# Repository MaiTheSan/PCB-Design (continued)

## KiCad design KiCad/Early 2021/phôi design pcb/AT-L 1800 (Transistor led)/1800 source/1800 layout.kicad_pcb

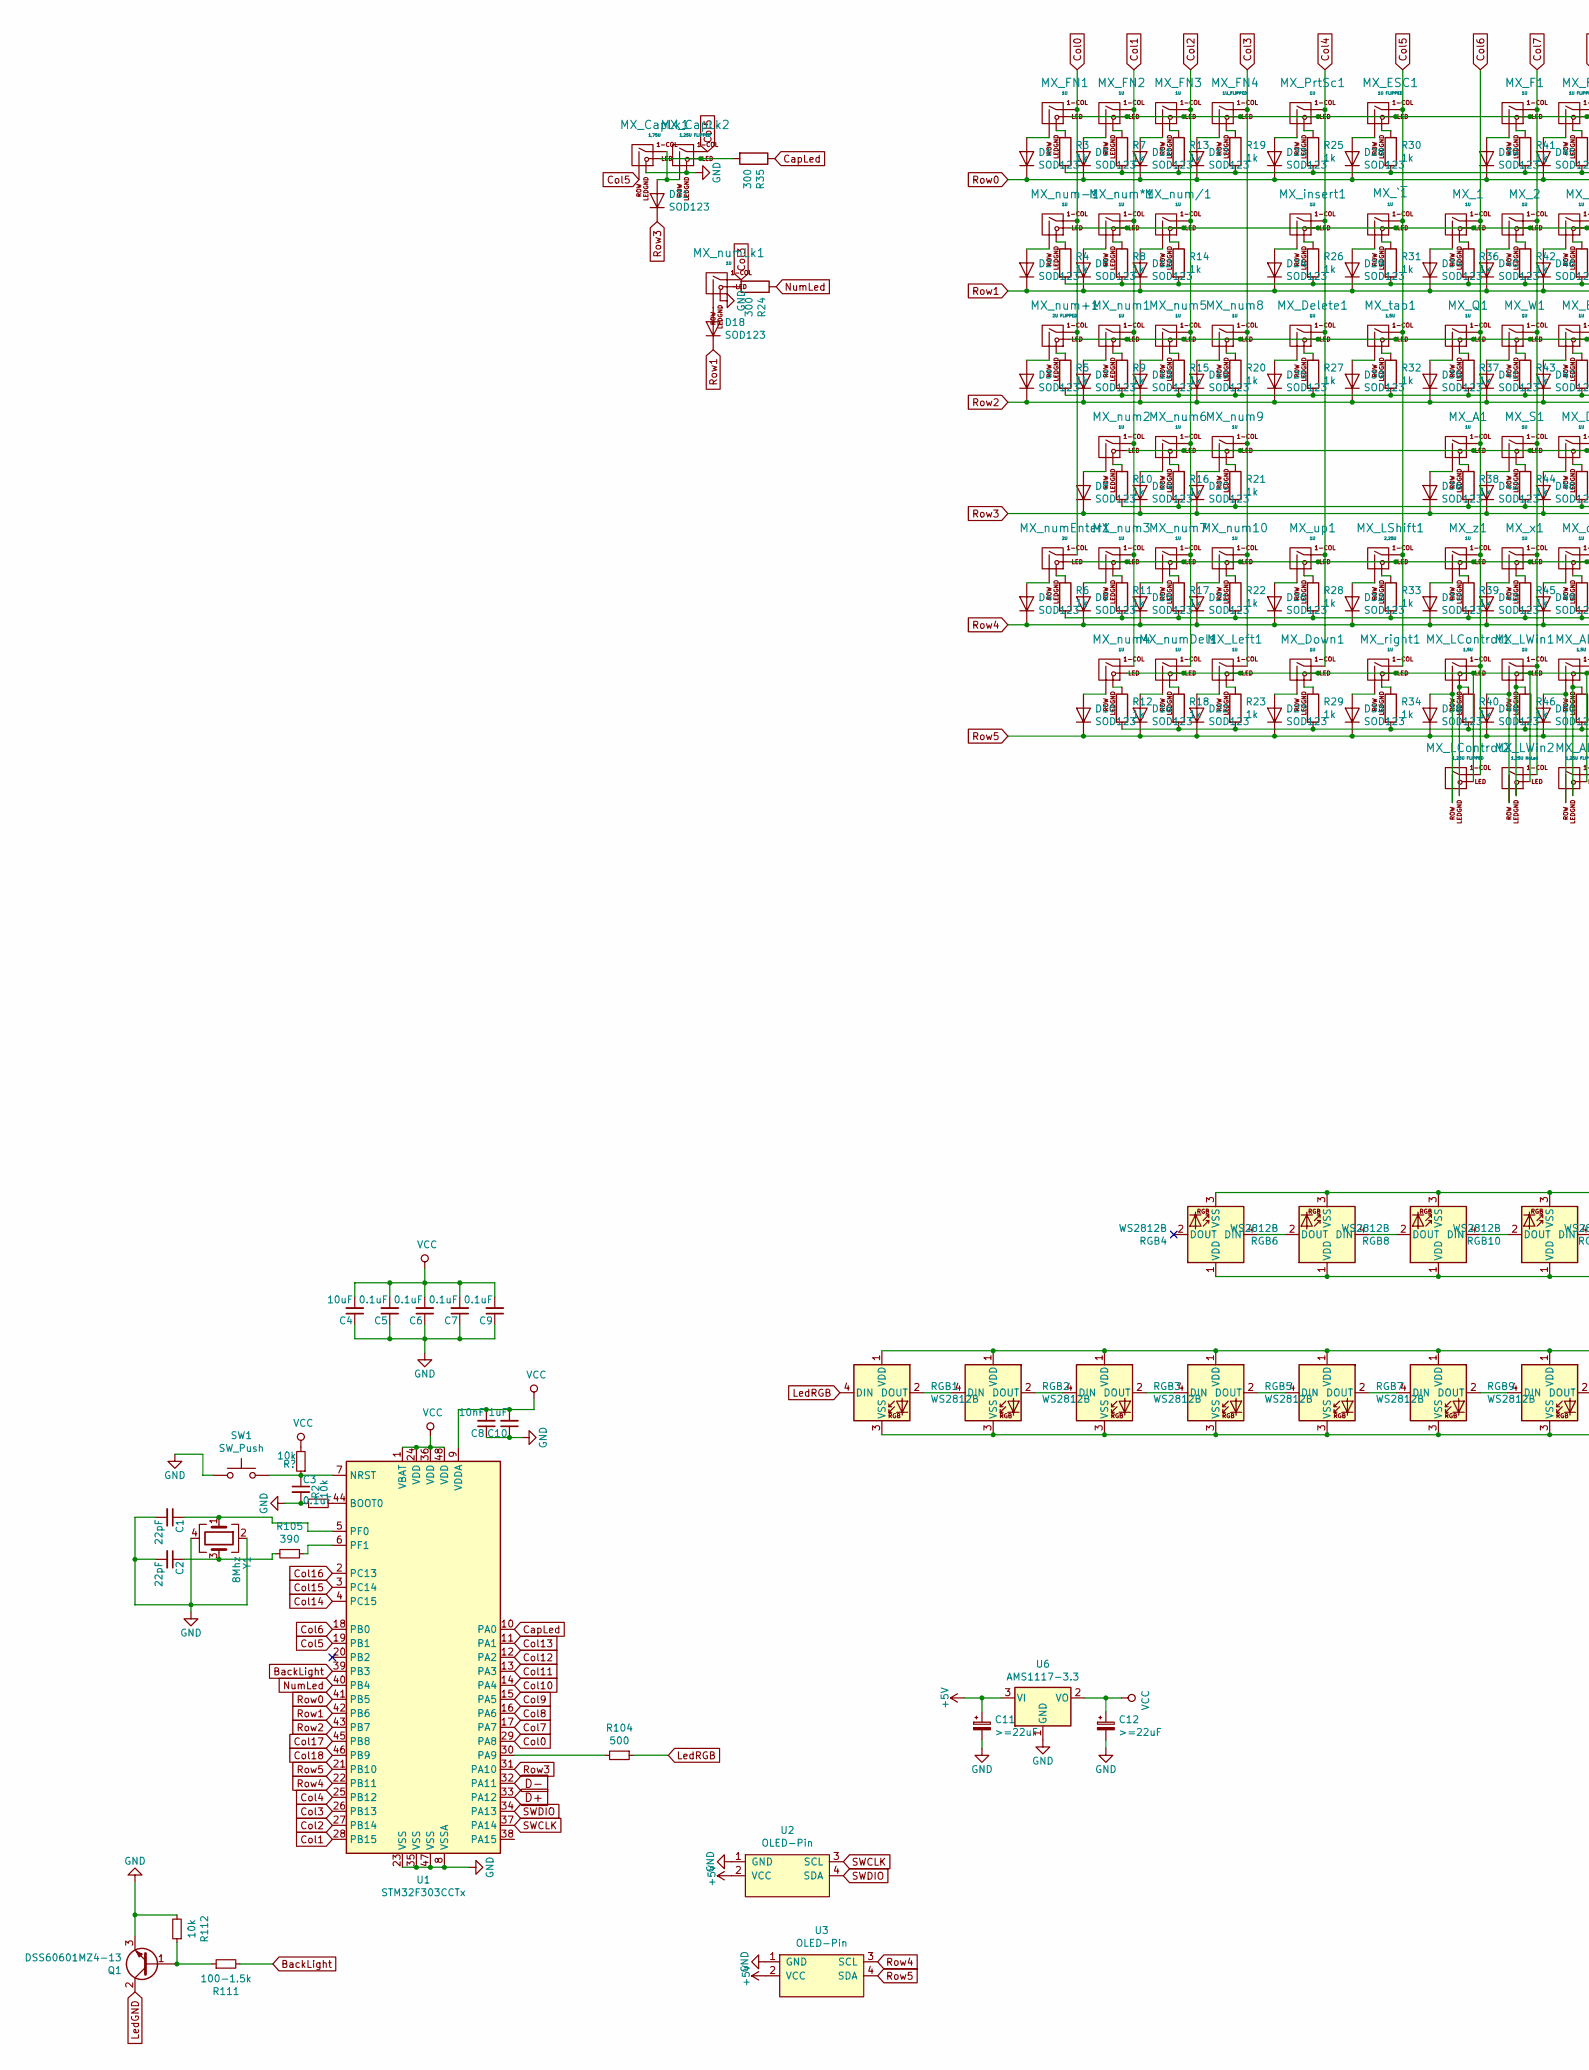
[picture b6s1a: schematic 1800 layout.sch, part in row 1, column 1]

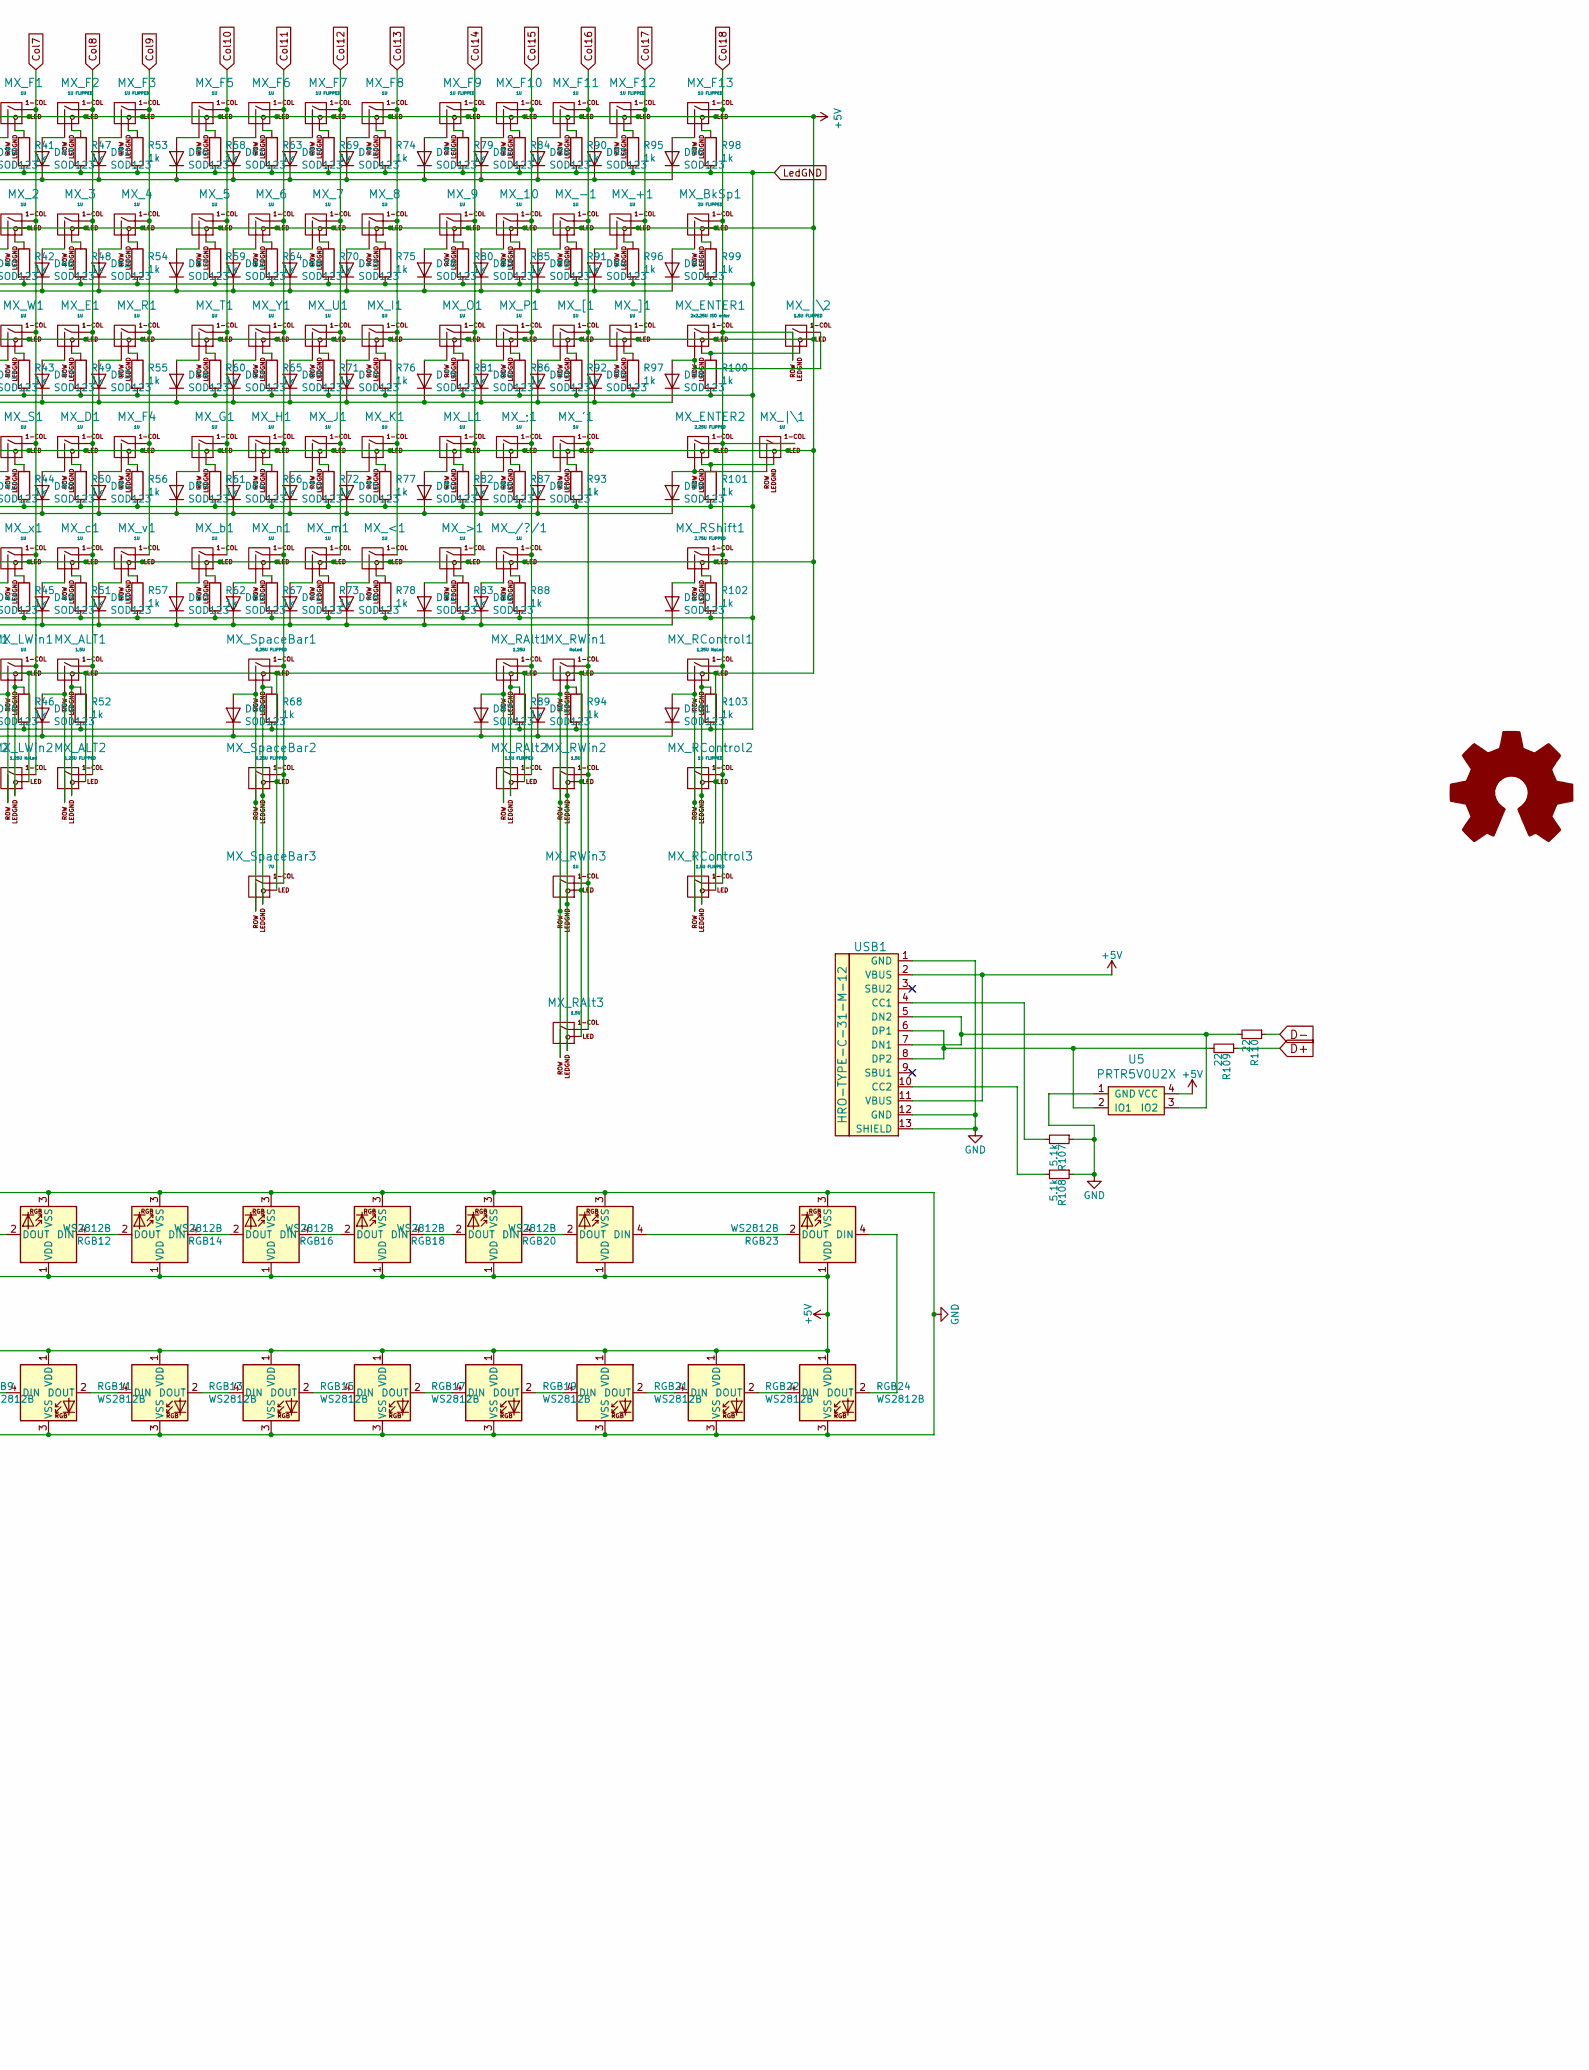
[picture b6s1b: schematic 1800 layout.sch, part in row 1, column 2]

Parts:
C1, C2: 22pF; C_0603
C3, C5, C6, C7, C9: 0.1uF; C_0402_1005Metric
C4: 10uF; C_0603
C8: 10nF; C_0402_1005Metric
C10: 1uF; C_0603
C11, C12: >=22uF; CP_EIA-3216-12_Kemet-S
D1, D2, D3, D4, D5, D6, D7, D8, D9, D10, D11, D12, D13, D14, D15, D16, D17, D18, D19, D20, D21, D22, D23, D24, D25, D26, D27, D28, D29, D30, D31, D32, D33, D34, D35, D36, D37, D38, D39, D40, D41, D42, D43, D44, D45, D46, D47, D48, D49, D50, D51, D52, D53, D54, D55, D56, D57, D58, D59, D60, D61, D62, D63, D64, D65, D66, D67, D68, D69, D70, D71, D72, D73, D74, D75, D76, D77, D78, D79, D80, D81, D82, D83, D84, D85, D86, D87, D88, D89, D90, D91, D92, D93, D94, D95, D96, D97, D98, D99, D101: SOD123; D_SOD-123
D100: SOD123; D_SOD-123-Pretty
LOGO1: Logo_Open_Hardware_Large; sanpjxlogo
MX_1, MX_2, MX_3, MX_4, MX_5, MX_6, MX_7, MX_8, MX_9, MX_10: 1U; MXOnly-1U
MX_'1: 1U; MXOnly-1U
MX_+1: 1U; MXOnly-1U
MX_-1: 1U; MXOnly-1U
MX_/?/1: 1U; MXOnly-1U
MX_;1: 1U; MXOnly-1U
MX_<1: 1U; MXOnly-1U
MX_>1: 1U; MXOnly-1U
MX_A1: 1U; MXOnly-1U
MX_ALT1: 1,5U; MXOnly-1.5U
MX_ALT2: 1,25U FLIPPED; MXOnly-1.25U-FLIPPED
MX_BkSp1: 2U FLIPPED; MXOnly-2U-FLIPPED
MX_CapLk1: 1,75U; MXOnly-1.75U-FLIPPED
MX_CapLk2: 1,25U FLIPPED; MXOnly-1.25U
MX_D1: 1U; MXOnly-1U
MX_Delete1: 1U; MXOnly-1U
MX_Down1: 1U; MXOnly-1U-FLIPPED
MX_E1: 1U; MXOnly-1U
MX_ENTER1: 2x2.25U ISO enter; MXOnly-ISO
MX_ENTER2: 2,25U FLIPPED; MXOnly-2.25U-FLIPPED-ReversedStabilizers
MX_ESC1: 1U FLIPPED; MXOnly-1U-FLIPPED
MX_F1, MX_F4, MX_F6, MX_F8, MX_F10, MX_F11: 1U; MXOnly-1U
MX_F2, MX_F3, MX_F7, MX_F9, MX_F12, MX_F13: 1U FLIPPED; MXOnly-1U-FLIPPED
MX_F5: 1U; MXOnly-1U-FLIPPED
MX_FN1, MX_FN2, MX_FN3: 1U; MXOnly-1U
MX_FN4: 1U_FLIPPED; MXOnly-1U-FLIPPED
MX_G1: 1U; MXOnly-1U
MX_H1: 1U; MXOnly-1U
MX_I1: 1U; MXOnly-1U
MX_J1: 1U; MXOnly-1U
MX_K1: 1U; MXOnly-1U
MX_L1: 1U; MXOnly-1U
MX_LControl1: 1,5U; MXOnly-1.5U
MX_LControl2: 1,25U FLIPPED; MXOnly-1.25U-FLIPPED
MX_LShift1: 2,25U; MXOnly-2.25U
MX_LWin1: 1U; MXOnly-1U
MX_LWin2: 1,25U NoLed; MXOnly-1.25U-FLIPPED
MX_Left1: 1U; MXOnly-1U
MX_O1: 1U; MXOnly-1U
MX_P1: 1U; MXOnly-1U
MX_PrtSc1: 1U; MXOnly-1U
MX_Q1: 1U; MXOnly-1U
MX_R1: 1U; MXOnly-1U
MX_RAlt1: 1,25U; MXOnly-1.25U
MX_RAlt2: 1,5U FLIPPED; MXOnly-1.5U-FLIPPED
MX_RAlt3: 1,5U; MXOnly-1.5U
MX_RControl1: 1,25U NoLed; MXOnly-1.25U
MX_RControl2: 1U FLIPPED; MXOnly-1U-FLIPPED
MX_RControl3: 1,5U FLIPPED; MXOnly-1.5U-FLIPPED
MX_RShift1: 2,75U FLIPPED; MXOnly-2.75U-FLIPPED
MX_RWin1: NoLed; MXOnly-1.25U-FLIPPED
MX_RWin2: 1,5U; MXOnly-1.5U
MX_RWin3: 1U; MXOnly-1U
MX_S1: 1U; MXOnly-1U
MX_SpaceBar1, MX_SpaceBar2: 6,25U FLIPPED; MXOnly-6.25U-FLIPPED-ReversedStabilizers
MX_SpaceBar3: 7U; MXOnly-7U-ReversedStabilizers
MX_T1: 1U; MXOnly-1U
MX_U1: 1U; MXOnly-1U
MX_W1: 1U; MXOnly-1U
MX_Y1: 1U; MXOnly-1U
MX_[1: 1U; MXOnly-1U
MX_]1: 1U; MXOnly-1U
MX_`~1: 1U; MXOnly-1U
MX_b1: 1U; MXOnly-1U
MX_c1: 1U; MXOnly-1U
MX_insert1: 1U; MXOnly-1U
MX_m1: 1U; MXOnly-1U
MX_n1: 1U; MXOnly-1U
MX_num1, MX_num2, MX_num3, MX_num4, MX_num5, MX_num6, MX_num7, MX_num9, MX_num10: 1U; MXOnly-1U
MX_num8: 1U; MXOnly-1U-FLIPPED
MX_num*1: 1U; MXOnly-1U
MX_num+1: 2U FLIPPED; MXOnly-2U
MX_num-1: 1U; MXOnly-1U
MX_num/1: 1U; MXOnly-1U
MX_numDel1: 1U; MXOnly-1U
MX_numEnter1: 2U; MXOnly-2U
MX_numLk1: 1U; MXOnly-1U-FLIPPED
MX_right1: 1U; MXOnly-1U
MX_tab1: 1,5U; MXOnly-1.5U
MX_up1: 1U; MXOnly-1U
MX_v1: 1U; MXOnly-1U
MX_x1: 1U; MXOnly-1U
MX_z1: 1U; MXOnly-1U
MX_|\1: 1U; MXOnly-1U
MX_|\2: 1.5U FLIPPED; MXOnly-1.5U-FLIPPED
Q1: DSS60601MZ4-13; SOT-223-3_TabPin2
R2: 10k; C_0603
R3, R4, R5, R6, R7, R8, R9, R10, R11, R12, R13, R14, R15, R16, R17, R18, R19, R20, R21, R22, R23, R25, R26, R27, R28, R29, R30, R31, R32, R33, R34, R36, R37, R38, R39, R40, R41, R42, R43, R44, R45, R46, R47, R48, R49, R50, R51, R52, R53, R54, R55, R56, R57, R58, R59, R60, R61, R62, R63, R64, R65, R66, R67, R68, R69, R70, R71, R72, R73, R74, R75, R76, R77, R78, R79, R80, R81, R82, R83, R84, R85, R86, R87, R88, R89, R90, R91, R92, R93, R94, R95, R96, R97, R98, R99, R100, R101, R102, R103: 1k; R_0805
R24, R35: 300; R_0805
R104: 500; R_0805
R105: 390; C_0603
R107, R108: 5.1k; C_0603
R109, R110: 22; C_0603
R111: 100-1.5k; R_0805
R112: 10k; R_0805
RGB1, RGB2, RGB3, RGB4, RGB5, RGB6, RGB7, RGB8, RGB9, RGB10, RGB11, RGB12, RGB13, RGB14, RGB15, RGB16, RGB17, RGB18, RGB19, RGB20, RGB21, RGB22, RGB23, RGB24: WS2812B; LED_WS2812B_PLCC4_5.0x5.0mm_P3.2mm
SW1: SW_Push; SKQG-1155865
U1: STM32F303CCTx; LQFP-48_7x7mm_P0.5mm
U2, U3: OLED-Pin; 0.91_SSD1306_OLED
U5: PRTR5V0U2X; SOT143B
U6: AMS1117-3.3; SOT-223-3_TabPin2
USB1: HRO-TYPE-C-31-M-12; HRO-TYPE-C-31-M-12-Assembly
Y1: 8Mhz; Crystal_SMD_3225-4Pin_3.2x2.5mm

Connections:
+5V: C11.1, MX_1.3 (LED), MX_2.3 (LED), MX_3.3 (LED), MX_4.3 (LED), MX_5.3 (LED), MX_6.3 (LED), MX_7.3 (LED), MX_8.3 (LED), MX_9.3 (LED), MX_10.3 (LED), MX_'1.3 (LED), MX_+1.3 (LED), MX_-1.3 (LED), MX_/?/1.3 (LED), MX_;1.3 (LED), MX_<1.3 (LED), MX_>1.3 (LED), MX_A1.3 (LED), MX_ALT1.3 (LED), MX_ALT2.3 (LED), MX_BkSp1.3 (LED), MX_D1.3 (LED), MX_Delete1.3 (LED), MX_Down1.3 (LED), MX_E1.3 (LED), MX_ENTER1.3 (LED), MX_ENTER2.3 (LED), MX_ESC1.3 (LED), MX_F1.3 (LED), MX_F2.3 (LED), MX_F3.3 (LED), MX_F4.3 (LED), MX_F5.3 (LED), MX_F6.3 (LED), MX_F7.3 (LED), MX_F8.3 (LED), MX_F9.3 (LED), MX_F10.3 (LED), MX_F11.3 (LED), MX_F12.3 (LED), MX_F13.3 (LED), MX_FN1.3 (LED), MX_FN2.3 (LED), MX_FN3.3 (LED), MX_FN4.3 (LED), MX_G1.3 (LED), MX_H1.3 (LED), MX_I1.3 (LED), MX_J1.3 (LED), MX_K1.3 (LED), MX_L1.3 (LED), MX_LControl1.3 (LED), MX_LControl2.3 (LED), MX_LShift1.3 (LED), MX_LWin1.3 (LED), MX_LWin2.3 (LED), MX_Left1.3 (LED), MX_O1.3 (LED), MX_P1.3 (LED), MX_PrtSc1.3 (LED), MX_Q1.3 (LED), MX_R1.3 (LED), MX_RAlt1.3 (LED), MX_RAlt2.3 (LED), MX_RAlt3.3 (LED), MX_RControl1.3 (LED), MX_RControl2.3 (LED), MX_RControl3.3 (LED), MX_RShift1.3 (LED), MX_RWin1.3 (LED), MX_RWin2.3 (LED), MX_RWin3.3 (LED), MX_S1.3 (LED), MX_SpaceBar1.3 (LED), MX_SpaceBar2.3 (LED), MX_SpaceBar3.3 (LED), MX_T1.3 (LED), MX_U1.3 (LED), MX_W1.3 (LED), MX_Y1.3 (LED), MX_[1.3 (LED), MX_]1.3 (LED), MX_`~1.3 (LED), MX_b1.3 (LED), MX_c1.3 (LED), MX_insert1.3 (LED), MX_m1.3 (LED), MX_n1.3 (LED), MX_num1.3 (LED), MX_num2.3 (LED), MX_num3.3 (LED), MX_num4.3 (LED), MX_num5.3 (LED), MX_num6.3 (LED), MX_num7.3 (LED), MX_num8.3 (LED), MX_num9.3 (LED), MX_num10.3 (LED), MX_num*1.3 (LED), MX_num+1.3 (LED), MX_num-1.3 (LED), MX_num/1.3 (LED), MX_numDel1.3 (LED), MX_numEnter1.3 (LED), MX_right1.3 (LED), MX_tab1.3 (LED), MX_up1.3 (LED), MX_v1.3 (LED), MX_x1.3 (LED), MX_z1.3 (LED), MX_|\1.3 (LED), MX_|\2.3 (LED), RGB1.1 (VDD), RGB2.1 (VDD), RGB3.1 (VDD), RGB4.1 (VDD), RGB5.1 (VDD), RGB6.1 (VDD), RGB7.1 (VDD), RGB8.1 (VDD), RGB9.1 (VDD), RGB10.1 (VDD), RGB11.1 (VDD), RGB12.1 (VDD), RGB13.1 (VDD), RGB14.1 (VDD), RGB15.1 (VDD), RGB16.1 (VDD), RGB17.1 (VDD), RGB18.1 (VDD), RGB19.1 (VDD), RGB20.1 (VDD), RGB21.1 (VDD), RGB22.1 (VDD), RGB23.1 (VDD), RGB24.1 (VDD), U2.2 (VCC), U3.2 (VCC), U5.4 (VCC), U6.3 (VI), USB1.2 (VBUS), USB1.11 (VBUS)
BackLight: R111.2, U1.39 (PB3)
CapLed: R35.1, U1.10 (PA0)
Col0: MX_FN1.1 (COL), MX_num+1.1 (COL), MX_num-1.1 (COL), MX_numEnter1.1 (COL), U1.29 (PA8)
Col1: MX_FN2.1 (COL), MX_num1.1 (COL), MX_num2.1 (COL), MX_num3.1 (COL), MX_num4.1 (COL), MX_num*1.1 (COL), U1.28 (PB15)
Col2: MX_FN3.1 (COL), MX_num5.1 (COL), MX_num6.1 (COL), MX_num7.1 (COL), MX_num/1.1 (COL), MX_numDel1.1 (COL), U1.27 (PB14)
Col3: MX_FN4.1 (COL), MX_Left1.1 (COL), MX_num8.1 (COL), MX_num9.1 (COL), MX_num10.1 (COL), MX_numLk1.1 (COL), U1.26 (PB13)
Col4: MX_Delete1.1 (COL), MX_Down1.1 (COL), MX_PrtSc1.1 (COL), MX_insert1.1 (COL), MX_up1.1 (COL), U1.25 (PB12)
Col5: MX_CapLk1.2 (ROW), MX_CapLk2.1 (COL), MX_ESC1.1 (COL), MX_LShift1.1 (COL), MX_`~1.1 (COL), MX_right1.1 (COL), MX_tab1.1 (COL), U1.19 (PB1)
Col6: MX_1.1 (COL), MX_A1.1 (COL), MX_LControl1.1 (COL), MX_LControl2.1 (COL), MX_Q1.1 (COL), MX_z1.1 (COL), U1.18 (PB0)
Col7: MX_2.1 (COL), MX_F1.1 (COL), MX_LWin1.1 (COL), MX_LWin2.1 (COL), MX_S1.1 (COL), MX_W1.1 (COL), MX_x1.1 (COL), U1.17 (PA7)
Col8: MX_3.1 (COL), MX_ALT1.1 (COL), MX_ALT2.1 (COL), MX_D1.1 (COL), MX_E1.1 (COL), MX_F2.1 (COL), MX_c1.1 (COL), U1.16 (PA6)
Col9: MX_4.1 (COL), MX_F3.1 (COL), MX_F4.1 (COL), MX_R1.1 (COL), MX_v1.1 (COL), U1.15 (PA5)
Col10: MX_5.1 (COL), MX_F5.1 (COL), MX_G1.1 (COL), MX_T1.1 (COL), MX_b1.1 (COL), U1.14 (PA4)
Col11: MX_6.1 (COL), MX_F6.1 (COL), MX_H1.1 (COL), MX_SpaceBar1.1 (COL), MX_SpaceBar2.1 (COL), MX_SpaceBar3.1 (COL), MX_Y1.1 (COL), MX_n1.1 (COL), U1.13 (PA3)
Col12: MX_7.1 (COL), MX_F7.1 (COL), MX_J1.1 (COL), MX_U1.1 (COL), MX_m1.1 (COL), U1.12 (PA2)
Col13: MX_8.1 (COL), MX_<1.1 (COL), MX_F8.1 (COL), MX_I1.1 (COL), MX_K1.1 (COL), U1.11 (PA1)
Col14: MX_9.1 (COL), MX_>1.1 (COL), MX_F9.1 (COL), MX_L1.1 (COL), MX_O1.1 (COL), U1.4 (PC15)
Col15: MX_10.1 (COL), MX_/?/1.1 (COL), MX_;1.1 (COL), MX_F10.1 (COL), MX_P1.1 (COL), MX_RAlt1.1 (COL), MX_RAlt2.1 (COL), U1.3 (PC14)
Col16: MX_'1.1 (COL), MX_-1.1 (COL), MX_F11.1 (COL), MX_RAlt3.1 (COL), MX_RWin1.1 (COL), MX_RWin2.1 (COL), MX_RWin3.1 (COL), MX_[1.1 (COL), U1.2 (PC13)
Col17: MX_+1.1 (COL), MX_F12.1 (COL), MX_]1.1 (COL), U1.45 (PB8)
Col18: MX_BkSp1.1 (COL), MX_ENTER1.1 (COL), MX_ENTER2.1 (COL), MX_F13.1 (COL), MX_RControl1.1 (COL), MX_RControl2.1 (COL), MX_RControl3.1 (COL), MX_RShift1.1 (COL), MX_|\1.1 (COL), MX_|\2.2 (ROW), U1.46 (PB9)
D+: R109.1, U1.33 (PA12)
D-: R110.1, U1.32 (PA11)
GND: C1.2, C2.2, C3.2, C4.1, C5.1, C6.1, C7.1, C8.1, C9.1, C10.1, C11.2, C12.2, MX_CapLk1.4 (LEDGND), MX_CapLk2.4 (LEDGND), MX_numLk1.4 (LEDGND), Q1.3 (E), R2.1, R107.1, R108.1, R112.2, RGB1.3 (VSS), RGB2.3 (VSS), RGB3.3 (VSS), RGB4.3 (VSS), RGB5.3 (VSS), RGB6.3 (VSS), RGB7.3 (VSS), RGB8.3 (VSS), RGB9.3 (VSS), RGB10.3 (VSS), RGB11.3 (VSS), RGB12.3 (VSS), RGB13.3 (VSS), RGB14.3 (VSS), RGB15.3 (VSS), RGB16.3 (VSS), RGB17.3 (VSS), RGB18.3 (VSS), RGB19.3 (VSS), RGB20.3 (VSS), RGB21.3 (VSS), RGB22.3 (VSS), RGB23.3 (VSS), RGB24.3 (VSS), SW1.1, U1.8 (VSSA), U1.23 (VSS), U1.35 (VSS), U1.47 (VSS), U2.1 (GND), U3.1 (GND), U5.1 (GND), U6.1 (GND), USB1.1 (GND), USB1.12 (GND), USB1.13 (SHIELD), Y1.2, Y1.4
LedGND: Q1.2 (C), R3.2, R4.2, R5.2, R6.2, R7.2, R8.2, R9.2, R10.2, R11.2, R12.2, R13.2, R14.2, R15.2, R16.2, R17.2, R18.2, R19.2, R20.2, R21.2, R22.2, R23.2, R25.2, R26.2, R27.2, R28.2, R29.2, R30.2, R31.2, R32.2, R33.2, R34.2, R36.2, R37.2, R38.2, R39.2, R40.2, R41.2, R42.2, R43.2, R44.2, R45.2, R46.2, R47.2, R48.2, R49.2, R50.2, R51.2, R52.2, R53.2, R54.2, R55.2, R56.2, R57.2, R58.2, R59.2, R60.2, R61.2, R62.2, R63.2, R64.2, R65.2, R66.2, R67.2, R68.2, R69.2, R70.2, R71.2, R72.2, R73.2, R74.2, R75.2, R76.2, R77.2, R78.2, R79.2, R80.2, R81.2, R82.2, R83.2, R84.2, R85.2, R86.2, R87.2, R88.2, R89.2, R90.2, R91.2, R92.2, R93.2, R94.2, R95.2, R96.2, R97.2, R98.2, R99.2, R100.2, R101.2, R102.2, R103.2
LedRGB: R104.1, RGB1.4 (DIN)
unnamed: C1.1, U1.5 (PF0), Y1.1
unnamed: C2.1, R105.2, Y1.3
unnamed: C3.1, SW1.2, U1.7 (NRST)
unnamed: D1.2 (A), MX_FN1.2 (ROW)
unnamed: D2.2 (A), MX_num-1.2 (ROW)
unnamed: D3.2 (A), MX_num+1.2 (ROW)
unnamed: D4.2 (A), MX_numEnter1.2 (ROW)
unnamed: D5.2 (A), MX_FN2.2 (ROW)
unnamed: D6.2 (A), MX_num*1.2 (ROW)
unnamed: D7.2 (A), MX_num1.2 (ROW)
unnamed: D8.2 (A), MX_num2.2 (ROW)
unnamed: D9.2 (A), MX_num3.2 (ROW)
unnamed: D10.2 (A), MX_num4.2 (ROW)
unnamed: D11.2 (A), MX_FN3.2 (ROW)
unnamed: D12.2 (A), MX_num/1.2 (ROW)
unnamed: D13.2 (A), MX_num5.2 (ROW)
unnamed: D14.2 (A), MX_num6.2 (ROW)
unnamed: D15.2 (A), MX_num7.2 (ROW)
unnamed: D16.2 (A), MX_numDel1.2 (ROW)
unnamed: D17.2 (A), MX_FN4.2 (ROW)
unnamed: D18.2 (A), MX_numLk1.2 (ROW)
unnamed: D19.2 (A), MX_num8.2 (ROW)
unnamed: D20.2 (A), MX_num9.2 (ROW)
unnamed: D21.2 (A), MX_num10.2 (ROW)
unnamed: D22.2 (A), MX_Left1.2 (ROW)
unnamed: D23.2 (A), MX_PrtSc1.2 (ROW)
unnamed: D24.2 (A), MX_insert1.2 (ROW)
unnamed: D25.2 (A), MX_Delete1.2 (ROW)
unnamed: D26.2 (A), MX_up1.2 (ROW)
unnamed: D27.2 (A), MX_Down1.2 (ROW)
unnamed: D28.2 (A), MX_ESC1.2 (ROW)
unnamed: D29.2 (A), MX_`~1.2 (ROW)
unnamed: D30.2 (A), MX_tab1.2 (ROW)
unnamed: D31.2 (A), MX_CapLk1.1 (COL), MX_CapLk2.2 (ROW)
unnamed: D32.2 (A), MX_LShift1.2 (ROW)
unnamed: D33.2 (A), MX_right1.2 (ROW)
unnamed: D34.2 (A), MX_1.2 (ROW)
unnamed: D35.2 (A), MX_Q1.2 (ROW)
unnamed: D36.2 (A), MX_A1.2 (ROW)
unnamed: D37.2 (A), MX_z1.2 (ROW)
unnamed: D38.2 (A), MX_LControl1.2 (ROW), MX_LControl2.2 (ROW)
unnamed: D39.2 (A), MX_F1.2 (ROW)
unnamed: D40.2 (A), MX_2.2 (ROW)
unnamed: D41.2 (A), MX_W1.2 (ROW)
unnamed: D42.2 (A), MX_S1.2 (ROW)
unnamed: D43.2 (A), MX_x1.2 (ROW)
unnamed: D44.2 (A), MX_LWin1.2 (ROW), MX_LWin2.2 (ROW)
unnamed: D45.2 (A), MX_F2.2 (ROW)
unnamed: D46.2 (A), MX_3.2 (ROW)
unnamed: D47.2 (A), MX_E1.2 (ROW)
unnamed: D48.2 (A), MX_D1.2 (ROW)
unnamed: D49.2 (A), MX_c1.2 (ROW)
unnamed: D50.2 (A), MX_ALT1.2 (ROW), MX_ALT2.2 (ROW)
unnamed: D51.2 (A), MX_F3.2 (ROW)
unnamed: D52.2 (A), MX_4.2 (ROW)
unnamed: D53.2 (A), MX_R1.2 (ROW)
unnamed: D54.2 (A), MX_F4.2 (ROW)
unnamed: D55.2 (A), MX_v1.2 (ROW)
unnamed: D56.2 (A), MX_F5.2 (ROW)
unnamed: D57.2 (A), MX_5.2 (ROW)
unnamed: D58.2 (A), MX_T1.2 (ROW)
unnamed: D59.2 (A), MX_G1.2 (ROW)
unnamed: D60.2 (A), MX_b1.2 (ROW)
unnamed: D61.2 (A), MX_F6.2 (ROW)
unnamed: D62.2 (A), MX_6.2 (ROW)
unnamed: D63.2 (A), MX_Y1.2 (ROW)
unnamed: D64.2 (A), MX_H1.2 (ROW)
unnamed: D65.2 (A), MX_n1.2 (ROW)
unnamed: D66.2 (A), MX_SpaceBar1.2 (ROW), MX_SpaceBar2.2 (ROW), MX_SpaceBar3.2 (ROW)
unnamed: D67.2 (A), MX_F7.2 (ROW)
unnamed: D68.2 (A), MX_7.2 (ROW)
unnamed: D69.2 (A), MX_U1.2 (ROW)
unnamed: D70.2 (A), MX_J1.2 (ROW)
unnamed: D71.2 (A), MX_m1.2 (ROW)
unnamed: D72.2 (A), MX_F8.2 (ROW)
unnamed: D73.2 (A), MX_8.2 (ROW)
unnamed: D74.2 (A), MX_I1.2 (ROW)
unnamed: D75.2 (A), MX_K1.2 (ROW)
unnamed: D76.2 (A), MX_<1.2 (ROW)
unnamed: D77.2 (A), MX_F9.2 (ROW)
unnamed: D78.2 (A), MX_9.2 (ROW)
unnamed: D79.2 (A), MX_O1.2 (ROW)
unnamed: D80.2 (A), MX_L1.2 (ROW)
unnamed: D81.2 (A), MX_>1.2 (ROW)
unnamed: D82.2 (A), MX_F10.2 (ROW)
unnamed: D83.2 (A), MX_10.2 (ROW)
unnamed: D84.2 (A), MX_P1.2 (ROW)
unnamed: D85.2 (A), MX_;1.2 (ROW)
unnamed: D86.2 (A), MX_/?/1.2 (ROW)
unnamed: D87.2 (A), MX_RAlt1.2 (ROW), MX_RAlt2.2 (ROW)
unnamed: D88.2 (A), MX_F11.2 (ROW)
unnamed: D89.2 (A), MX_-1.2 (ROW)
unnamed: D90.2 (A), MX_[1.2 (ROW)
unnamed: D91.2 (A), MX_'1.2 (ROW)
unnamed: D92.2 (A), MX_RAlt3.2 (ROW), MX_RWin1.2 (ROW), MX_RWin2.2 (ROW), MX_RWin3.2 (ROW)
unnamed: D93.2 (A), MX_F12.2 (ROW)
unnamed: D94.2 (A), MX_+1.2 (ROW)
unnamed: D95.2 (A), MX_]1.2 (ROW)
unnamed: D96.2 (A), MX_F13.2 (ROW)
unnamed: D97.2 (A), MX_BkSp1.2 (ROW)
unnamed: D98.2 (A), MX_ENTER1.2 (ROW), MX_|\2.1 (COL)
unnamed: D99.2 (A), MX_ENTER2.2 (ROW), MX_|\1.2 (ROW)
unnamed: D100.2 (A), MX_RShift1.2 (ROW)
unnamed: D101.2 (A), MX_RControl1.2 (ROW), MX_RControl2.2 (ROW), MX_RControl3.2 (ROW)
unnamed: MX_1.4 (LEDGND), R36.1
unnamed: MX_2.4 (LEDGND), R42.1
unnamed: MX_3.4 (LEDGND), R48.1
unnamed: MX_4.4 (LEDGND), R54.1
unnamed: MX_5.4 (LEDGND), R59.1
unnamed: MX_6.4 (LEDGND), R64.1
unnamed: MX_7.4 (LEDGND), R70.1
unnamed: MX_8.4 (LEDGND), R75.1
unnamed: MX_9.4 (LEDGND), R80.1
unnamed: MX_10.4 (LEDGND), R85.1
unnamed: MX_'1.4 (LEDGND), R93.1
unnamed: MX_+1.4 (LEDGND), R96.1
unnamed: MX_-1.4 (LEDGND), R91.1
unnamed: MX_/?/1.4 (LEDGND), R88.1
unnamed: MX_;1.4 (LEDGND), R87.1
unnamed: MX_<1.4 (LEDGND), R78.1
unnamed: MX_>1.4 (LEDGND), R83.1
unnamed: MX_A1.4 (LEDGND), R38.1
unnamed: MX_ALT1.4 (LEDGND), MX_ALT2.4 (LEDGND), R52.1
unnamed: MX_BkSp1.4 (LEDGND), R99.1
unnamed: MX_CapLk1.3 (LED), MX_CapLk2.3 (LED), R35.2
unnamed: MX_D1.4 (LEDGND), R50.1
unnamed: MX_Delete1.4 (LEDGND), R27.1
unnamed: MX_Down1.4 (LEDGND), R29.1
unnamed: MX_E1.4 (LEDGND), R49.1
unnamed: MX_ENTER1.4 (LEDGND), MX_|\2.4 (LEDGND), R100.1
unnamed: MX_ENTER2.4 (LEDGND), MX_|\1.4 (LEDGND), R101.1
unnamed: MX_ESC1.4 (LEDGND), R30.1
unnamed: MX_F1.4 (LEDGND), R41.1
unnamed: MX_F2.4 (LEDGND), R47.1
unnamed: MX_F3.4 (LEDGND), R53.1
unnamed: MX_F4.4 (LEDGND), R56.1
unnamed: MX_F5.4 (LEDGND), R58.1
unnamed: MX_F6.4 (LEDGND), R63.1
unnamed: MX_F7.4 (LEDGND), R69.1
unnamed: MX_F8.4 (LEDGND), R74.1
unnamed: MX_F9.4 (LEDGND), R79.1
unnamed: MX_F10.4 (LEDGND), R84.1
unnamed: MX_F11.4 (LEDGND), R90.1
unnamed: MX_F12.4 (LEDGND), R95.1
unnamed: MX_F13.4 (LEDGND), R98.1
unnamed: MX_FN1.4 (LEDGND), R3.1
unnamed: MX_FN2.4 (LEDGND), R7.1
unnamed: MX_FN3.4 (LEDGND), R13.1
unnamed: MX_FN4.4 (LEDGND), R19.1
unnamed: MX_G1.4 (LEDGND), R61.1
unnamed: MX_H1.4 (LEDGND), R66.1
unnamed: MX_I1.4 (LEDGND), R76.1
unnamed: MX_J1.4 (LEDGND), R72.1
unnamed: MX_K1.4 (LEDGND), R77.1
unnamed: MX_L1.4 (LEDGND), R82.1
unnamed: MX_LControl1.4 (LEDGND), MX_LControl2.4 (LEDGND), R40.1
unnamed: MX_LShift1.4 (LEDGND), R33.1
unnamed: MX_LWin1.4 (LEDGND), MX_LWin2.4 (LEDGND), R46.1
unnamed: MX_Left1.4 (LEDGND), R23.1
unnamed: MX_O1.4 (LEDGND), R81.1
unnamed: MX_P1.4 (LEDGND), R86.1
unnamed: MX_PrtSc1.4 (LEDGND), R25.1
unnamed: MX_Q1.4 (LEDGND), R37.1
unnamed: MX_R1.4 (LEDGND), R55.1
unnamed: MX_RAlt1.4 (LEDGND), MX_RAlt2.4 (LEDGND), R89.1
unnamed: MX_RAlt3.4 (LEDGND), MX_RWin1.4 (LEDGND), MX_RWin2.4 (LEDGND), MX_RWin3.4 (LEDGND), R94.1
unnamed: MX_RControl1.4 (LEDGND), MX_RControl2.4 (LEDGND), MX_RControl3.4 (LEDGND), R103.1
unnamed: MX_RShift1.4 (LEDGND), R102.1
unnamed: MX_S1.4 (LEDGND), R44.1
unnamed: MX_SpaceBar1.4 (LEDGND), MX_SpaceBar2.4 (LEDGND), MX_SpaceBar3.4 (LEDGND), R68.1
unnamed: MX_T1.4 (LEDGND), R60.1
unnamed: MX_U1.4 (LEDGND), R71.1
unnamed: MX_W1.4 (LEDGND), R43.1
unnamed: MX_Y1.4 (LEDGND), R65.1
unnamed: MX_[1.4 (LEDGND), R92.1
unnamed: MX_]1.4 (LEDGND), R97.1
unnamed: MX_`~1.4 (LEDGND), R31.1
unnamed: MX_b1.4 (LEDGND), R62.1
unnamed: MX_c1.4 (LEDGND), R51.1
unnamed: MX_insert1.4 (LEDGND), R26.1
unnamed: MX_m1.4 (LEDGND), R73.1
unnamed: MX_n1.4 (LEDGND), R67.1
unnamed: MX_num1.4 (LEDGND), R9.1
unnamed: MX_num2.4 (LEDGND), R10.1
unnamed: MX_num3.4 (LEDGND), R11.1
unnamed: MX_num4.4 (LEDGND), R12.1
unnamed: MX_num5.4 (LEDGND), R15.1
unnamed: MX_num6.4 (LEDGND), R16.1
unnamed: MX_num7.4 (LEDGND), R17.1
unnamed: MX_num8.4 (LEDGND), R20.1
unnamed: MX_num9.4 (LEDGND), R21.1
unnamed: MX_num10.4 (LEDGND), R22.1
unnamed: MX_num*1.4 (LEDGND), R8.1
unnamed: MX_num+1.4 (LEDGND), R5.1
unnamed: MX_num-1.4 (LEDGND), R4.1
unnamed: MX_num/1.4 (LEDGND), R14.1
unnamed: MX_numDel1.4 (LEDGND), R18.1
unnamed: MX_numEnter1.4 (LEDGND), R6.1
unnamed: MX_numLk1.3 (LED), R24.2
unnamed: MX_right1.4 (LEDGND), R34.1
unnamed: MX_tab1.4 (LEDGND), R32.1
unnamed: MX_up1.4 (LEDGND), R28.1
unnamed: MX_v1.4 (LEDGND), R57.1
unnamed: MX_x1.4 (LEDGND), R45.1
unnamed: MX_z1.4 (LEDGND), R39.1
unnamed: Q1.1 (B), R111.1, R112.1
unnamed: R2.2, U1.44 (BOOT0)
unnamed: R104.2, U1.30 (PA9)
unnamed: R105.1, U1.6 (PF1)
unnamed: R107.2, USB1.4 (CC1)
unnamed: R108.2, USB1.10 (CC2)
unnamed: R109.2, U5.2 (IO1), USB1.6 (DP1), USB1.8 (DP2)
unnamed: R110.2, U5.3 (IO2), USB1.5 (DN2), USB1.7 (DN1)
unnamed: RGB1.2 (DOUT), RGB2.4 (DIN)
unnamed: RGB2.2 (DOUT), RGB3.4 (DIN)
unnamed: RGB3.2 (DOUT), RGB5.4 (DIN)
unnamed: RGB4.4 (DIN), RGB6.2 (DOUT)
unnamed: RGB5.2 (DOUT), RGB7.4 (DIN)
unnamed: RGB6.4 (DIN), RGB8.2 (DOUT)
unnamed: RGB7.2 (DOUT), RGB9.4 (DIN)
unnamed: RGB8.4 (DIN), RGB10.2 (DOUT)
unnamed: RGB10.4 (DIN), RGB12.2 (DOUT)
unnamed: RGB11.2 (DOUT), RGB13.4 (DIN)
unnamed: RGB9.2 (DOUT), RGB11.4 (DIN)
unnamed: RGB12.4 (DIN), RGB14.2 (DOUT)
unnamed: RGB13.2 (DOUT), RGB15.4 (DIN)
unnamed: RGB14.4 (DIN), RGB16.2 (DOUT)
unnamed: RGB15.2 (DOUT), RGB17.4 (DIN)
unnamed: RGB16.4 (DIN), RGB18.2 (DOUT)
unnamed: RGB17.2 (DOUT), RGB19.4 (DIN)
unnamed: RGB18.4 (DIN), RGB20.2 (DOUT)
unnamed: RGB19.2 (DOUT), RGB21.4 (DIN)
unnamed: RGB20.4 (DIN), RGB23.2 (DOUT)
unnamed: RGB21.2 (DOUT), RGB22.4 (DIN)
unnamed: RGB22.2 (DOUT), RGB24.4 (DIN)
unnamed: RGB23.4 (DIN), RGB24.2 (DOUT)
NumLed: R24.1, U1.40 (PB4)
Row0: D1.1 (K), D5.1 (K), D11.1 (K), D17.1 (K), D23.1 (K), D28.1 (K), D39.1 (K), D45.1 (K), D51.1 (K), D56.1 (K), D61.1 (K), D67.1 (K), D72.1 (K), D77.1 (K), D82.1 (K), D88.1 (K), D93.1 (K), D96.1 (K), U1.41 (PB5)
Row1: D2.1 (K), D6.1 (K), D12.1 (K), D18.1 (K), D24.1 (K), D29.1 (K), D34.1 (K), D40.1 (K), D46.1 (K), D52.1 (K), D57.1 (K), D62.1 (K), D68.1 (K), D73.1 (K), D78.1 (K), D83.1 (K), D89.1 (K), D94.1 (K), D97.1 (K), U1.42 (PB6)
Row2: D3.1 (K), D7.1 (K), D13.1 (K), D19.1 (K), D25.1 (K), D30.1 (K), D35.1 (K), D41.1 (K), D47.1 (K), D53.1 (K), D58.1 (K), D63.1 (K), D69.1 (K), D74.1 (K), D79.1 (K), D84.1 (K), D90.1 (K), D95.1 (K), D98.1 (K), U1.43 (PB7)
Row3: D8.1 (K), D14.1 (K), D20.1 (K), D31.1 (K), D36.1 (K), D42.1 (K), D48.1 (K), D54.1 (K), D59.1 (K), D64.1 (K), D70.1 (K), D75.1 (K), D80.1 (K), D85.1 (K), D91.1 (K), D99.1 (K), U1.31 (PA10)
Row4: D4.1 (K), D9.1 (K), D15.1 (K), D21.1 (K), D26.1 (K), D32.1 (K), D37.1 (K), D43.1 (K), D49.1 (K), D55.1 (K), D60.1 (K), D65.1 (K), D71.1 (K), D76.1 (K), D81.1 (K), D86.1 (K), D100.1 (K), U1.22 (PB11), U3.3 (SCL)
Row5: D10.1 (K), D16.1 (K), D22.1 (K), D27.1 (K), D33.1 (K), D38.1 (K), D44.1 (K), D50.1 (K), D66.1 (K), D87.1 (K), D92.1 (K), D101.1 (K), U1.21 (PB10), U3.4 (SDA)
SWCLK: U1.37 (PA14), U2.3 (SCL)
SWDIO: U1.34 (PA13), U2.4 (SDA)
VCC: C4.2, C5.2, C6.2, C7.2, C8.2, C9.2, C10.2, C12.1, U1.1 (VBAT), U1.9 (VDDA), U1.24 (VDD), U1.36 (VDD), U1.48 (VDD), U6.2 (VO)

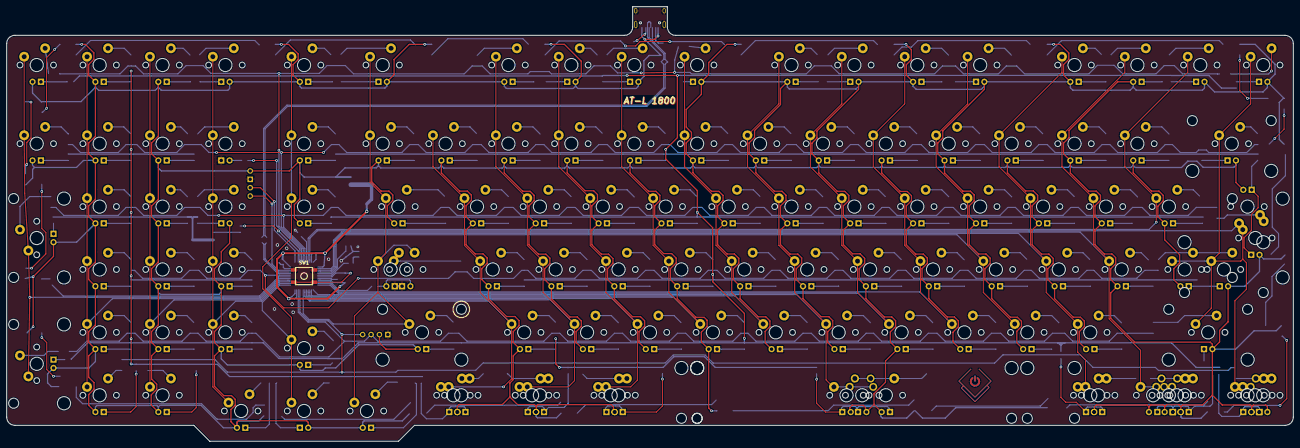
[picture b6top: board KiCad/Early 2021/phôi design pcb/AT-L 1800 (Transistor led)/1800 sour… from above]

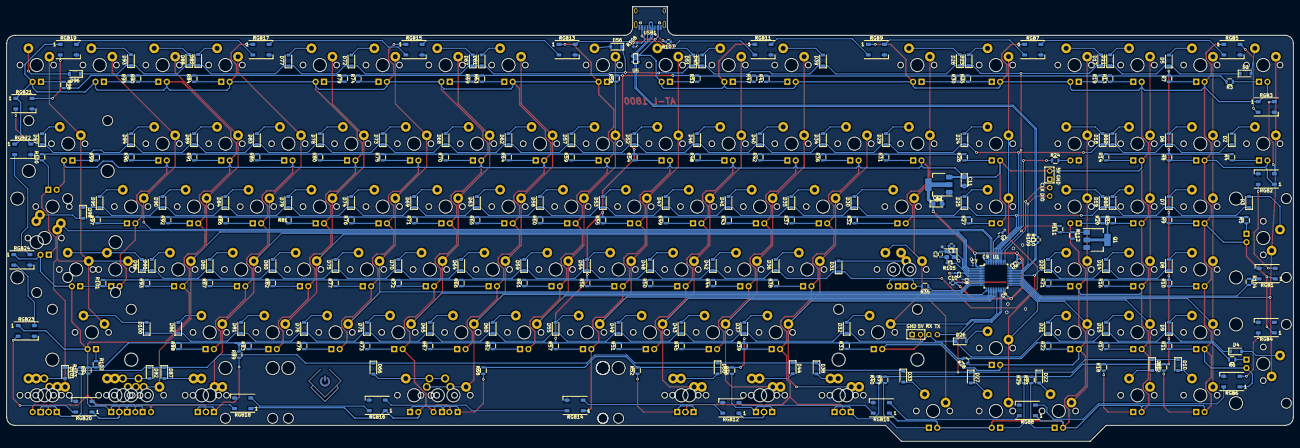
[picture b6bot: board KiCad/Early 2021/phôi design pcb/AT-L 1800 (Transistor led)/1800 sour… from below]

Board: 2 copper layers, 389.7 x 131.6 mm, 372 parts (253 on the bottom side), 273 nets.
